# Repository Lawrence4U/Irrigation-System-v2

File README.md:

# Irrigation System using LoRa communications and Chirpstack

### KiCad

The external footprints used can be found in the [Imports](./KiCad/symbols/Imports/) folder.

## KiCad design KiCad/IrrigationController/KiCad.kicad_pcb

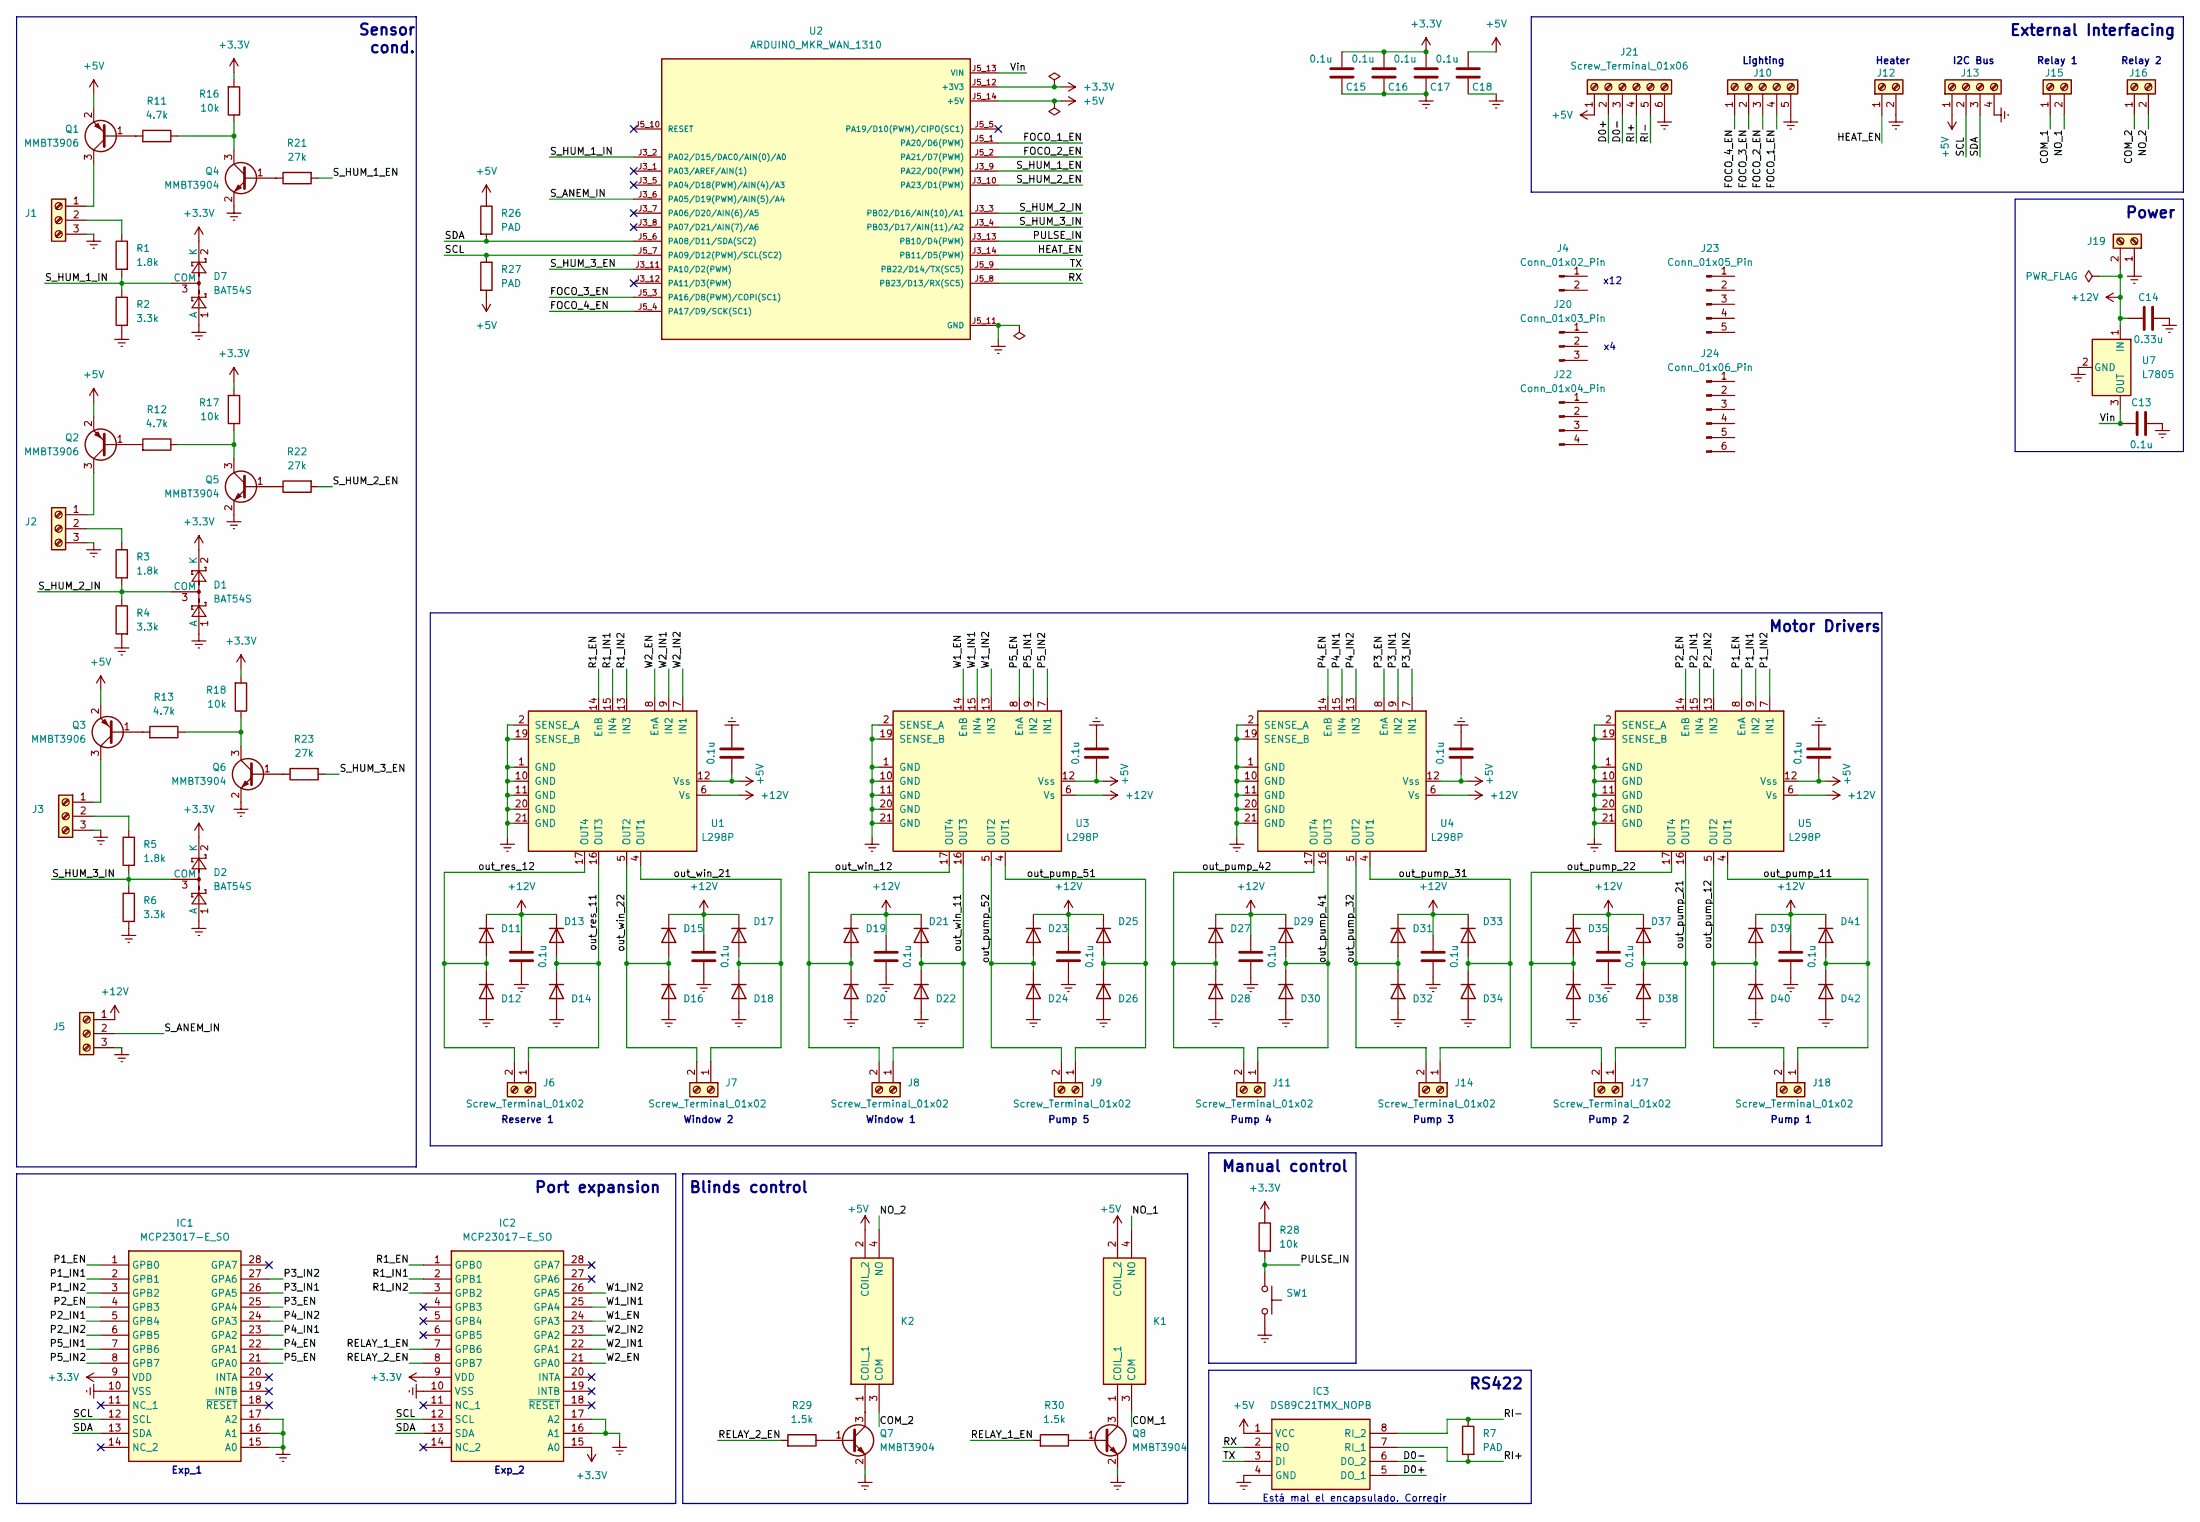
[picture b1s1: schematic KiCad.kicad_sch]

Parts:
C1, C2, C3, C4, C5, C6, C7, C8, C9, C10, C11, C12, C13, C15, C16, C17, C18: 0.1u; C_1206_3216Metric; Mouser Part Number 80-C1206X104K1RAUTO
C14: 0.33u; C_1206_3216Metric; Mouser Part Number 80-C1206X334K1RAUTO
D1, D2, D7: BAT54S; SOT-23; Mouser Part Number 637-BAT54S
D11, D12, D13, D14, D15, D16, D17, D18, D19, D20, D21, D22, D23, D24, D25, D26, D27, D28, D29, D30, D31, D32, D33, D34, D35, D36, D37, D38, D39, D40, D41, D42: SS24; D_SMB; Mouser Part Number 821-SS24
IC1, IC2: MCP23017-E_SO; SOIC127P1030X265-28N; Mouser Part Number 579-MCP23017-E/SO
IC3: DS89C21TMX_NOPB; SOIC127P600X175-8N; Mouser Part Number 926-DS89C21TMX/NOPB
J1, J2, J3, J5: Screw_Terminal_01x03; TerminalBlock_Phoenix_MKDS-1,5-3_1x03_P5.00mm_Horizontal; Mouser Part Number 710-691311700003
J4: Conn_01x02_Pin; Mouser Part Number 710-691352710002
J6, J7, J8, J9, J11, J12, J14, J15, J16, J17, J18, J19: Screw_Terminal_01x02; TerminalBlock_Phoenix_MKDS-1,5-2_1x02_P5.00mm_Horizontal; Mouser Part Number 710-691311700002
J10: Screw_Terminal_01x05; TerminalBlock_Phoenix_MKDS-1,5-5_1x05_P5.00mm_Horizontal; Mouser Part Number 710-691311700005
J13: Screw_Terminal_01x04; TerminalBlock_Phoenix_MKDS-1,5-4_1x04_P5.00mm_Horizontal; Mouser Part Number 710-691311700004
J20: Conn_01x03_Pin; Mouser Part Number 710-691352710003
J21: Screw_Terminal_01x06; TerminalBlock_Phoenix_MKDS-1,5-6_1x06_P5.00mm_Horizontal; Mouser Part Number 710-691311700006
J22: Conn_01x04_Pin; Mouser Part Number 710-691352710004
J23: Conn_01x05_Pin; Mouser Part Number 710-691352710005
J24: Conn_01x06_Pin; Mouser Part Number 710-691352710006
K1, K2: 2071556-9; 20715569; Mouser Part Number 655-2071556-9
Q1, Q2, Q3: MMBT3906; SOT-23
Q4, Q5, Q6, Q7, Q8: MMBT3904; SOT-23
R1, R3, R5: 1.8k; R_1206_3216Metric; Mouser Part Number 603-RT1206FRE071K8L
R2, R4, R6: 3.3k; R_1206_3216Metric; Mouser Part Number 603-RT1206FRE073K3L
R7, R26, R27: PAD; R_1206_3216Metric
R11, R12, R13: 4.7k; R_1206_3216Metric; Mouser Part Number 603-RT1206FRE074K7L
R16, R17, R18, R28: 10k; R_1206_3216Metric; Mouser Part Number 603-RT1206FRE1310KL
R21, R22, R23: 27k; R_1206_3216Metric; Mouser Part Number 603-RT1206FRE0727KL
R29, R30: 1.5k; R_1206_3216Metric; Mouser Part Number 603-RT1206FRE071K5L
SW1: SW_Push; SW_PUSH_6mm_H4.3mm
U1, U3, U4, U5: L298P; HSOP-20-1EP_11.0x15.9mm_P1.27mm_SlugDown_ThermalVias; Mouser Part Number 511-L298P
U2: ARDUINO_MKR_WAN_1310; BOARD_ARDUINO_MKR_WAN_1310; PARTREV 06/27/2019
U7: L7805; TO-263-2; Mouser Part Number 511-L7805ABD2T-TR

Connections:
+5V: C3.1, C6.1, C9.1, C12.1, C18.1, IC3.1 (VCC), J13.1, J21.1, K1.2 (COIL_2), K2.2 (COIL_2), Q1.2 (E), Q2.2 (E), Q3.2 (E), R26.1, R27.2, U1.12 (Vss), U2.J5_14 (+5V), U3.12 (Vss), U4.12 (Vss), U5.12 (Vss)
+12V: C1.1, C2.1, C4.1, C5.1, C7.1, C8.1, C10.1, C11.1, C14.1, D11.1 (K), D13.1 (K), D15.1 (K), D17.1 (K), D19.1 (K), D21.1 (K), D23.1 (K), D25.1 (K), D27.1 (K), D29.1 (K), D31.1 (K), D33.1 (K), D35.1 (K), D37.1 (K), D39.1 (K), D41.1 (K), J5.1, J19.2, U1.6 (Vs), U3.6 (Vs), U4.6 (Vs), U5.6 (Vs), U7.1 (IN)
/COM_1: J15.1, K1.3 (COM)
/COM_2: J16.1, K2.3 (COM)
/D0+: IC3.5 (DO_1), J21.2
/D0-: IC3.6 (DO_2), J21.3
/FOCO_1_EN: J10.4, U2.J5_1 (PA20/D6(PWM))
/FOCO_2_EN: J10.3, U2.J5_2 (PA21/D7(PWM))
/FOCO_3_EN: J10.2, U2.J5_3 (PA16/D8(PWM)/COPI(SC1))
/FOCO_4_EN: J10.1, U2.J5_4 (PA17/D9/SCK(SC1))
/HEAT_EN: J12.1, U2.J3_14 (PB11/D5(PWM))
/NO_1: J15.2, K1.4 (NO)
/NO_2: J16.2, K2.4 (NO)
/P1_EN: IC1.1 (GPB0), U5.8 (EnA)
/P1_IN1: IC1.2 (GPB1), U5.9 (IN2)
/P1_IN2: IC1.3 (GPB2), U5.7 (IN1)
/P2_EN: IC1.4 (GPB3), U5.14 (EnB)
/P2_IN1: IC1.5 (GPB4), U5.15 (IN4)
/P2_IN2: IC1.6 (GPB5), U5.13 (IN3)
/P3_EN: IC1.25 (GPA4), U4.8 (EnA)
/P3_IN1: IC1.26 (GPA5), U4.9 (IN2)
/P3_IN2: IC1.27 (GPA6), U4.7 (IN1)
/P4_EN: IC1.22 (GPA1), U4.14 (EnB)
/P4_IN1: IC1.23 (GPA2), U4.15 (IN4)
/P4_IN2: IC1.24 (GPA3), U4.13 (IN3)
/P5_EN: IC1.21 (GPA0), U3.8 (EnA)
/P5_IN1: IC1.7 (GPB6), U3.9 (IN2)
/P5_IN2: IC1.8 (GPB7), U3.7 (IN1)
/PULSE_IN: R28.2, SW1.1, U2.J3_13 (PB10/D4(PWM))
/R1_EN: IC2.1 (GPB0), U1.14 (EnB)
/R1_IN1: IC2.2 (GPB1), U1.15 (IN4)
/R1_IN2: IC2.3 (GPB2), U1.13 (IN3)
/RELAY_1_EN: IC2.7 (GPB6), R30.2
/RELAY_2_EN: IC2.8 (GPB7), R29.2
/RI+: IC3.7 (RI_1), J21.4, R7.2
/RI-: IC3.8 (RI_2), J21.5, R7.1
/RX: IC3.2 (RO), U2.J5_8 (PB23/D13/RX(SC5))
/SCL: IC1.12 (SCL), IC2.12 (SCL), J13.2, R27.1, U2.J5_7 (PA09/D12(PWM)/SCL(SC2))
/SDA: IC1.13 (SDA), IC2.13 (SDA), J13.3, R26.2, U2.J5_6 (PA08/D11/SDA(SC2))
/S_ANEM_IN: J5.2, U2.J3_6 (PA05/D19(PWM)/AIN(5)/A4)
/S_HUM_1_EN: R21.2, U2.J3_9 (PA22/D0(PWM))
/S_HUM_1_IN: D7.3 (COM), R1.2, R2.1, U2.J3_2 (PA02/D15/DAC0/AIN(0)/A0)
/S_HUM_2_EN: R22.2, U2.J3_10 (PA23/D1(PWM))
/S_HUM_2_IN: D1.3 (COM), R3.2, R4.1, U2.J3_3 (PB02/D16/AIN(10)/A1)
/S_HUM_3_EN: R23.2, U2.J3_11 (PA10/D2(PWM))
/S_HUM_3_IN: D2.3 (COM), R5.2, R6.1, U2.J3_4 (PB03/D17/AIN(11)/A2)
/TX: IC3.3 (DI), U2.J5_9 (PB22/D14/TX(SC5))
/W1_EN: IC2.24 (GPA3), U3.14 (EnB)
/W1_IN1: IC2.25 (GPA4), U3.15 (IN4)
/W1_IN2: IC2.26 (GPA5), U3.13 (IN3)
/W2_EN: IC2.21 (GPA0), U1.8 (EnA)
/W2_IN1: IC2.22 (GPA1), U1.9 (IN2)
/W2_IN2: IC2.23 (GPA2), U1.7 (IN1)
/out_pump_11: D41.2 (A), D42.1 (K), J18.1, U5.4 (OUT1)
/out_pump_12: D39.2 (A), D40.1 (K), J18.2, U5.5 (OUT2)
/out_pump_21: D37.2 (A), D38.1 (K), J17.1, U5.16 (OUT3)
/out_pump_22: D35.2 (A), D36.1 (K), J17.2, U5.17 (OUT4)
/out_pump_31: D33.2 (A), D34.1 (K), J14.1, U4.4 (OUT1)
/out_pump_32: D31.2 (A), D32.1 (K), J14.2, U4.5 (OUT2)
/out_pump_41: D29.2 (A), D30.1 (K), J11.1, U4.16 (OUT3)
/out_pump_42: D27.2 (A), D28.1 (K), J11.2, U4.17 (OUT4)
/out_pump_51: D25.2 (A), D26.1 (K), J9.1, U3.4 (OUT1)
/out_pump_52: D23.2 (A), D24.1 (K), J9.2, U3.5 (OUT2)
/out_res_11: D13.2 (A), D14.1 (K), J6.1, U1.16 (OUT3)
/out_res_12: D11.2 (A), D12.1 (K), J6.2, U1.17 (OUT4)
/out_win_11: D21.2 (A), D22.1 (K), J8.1, U3.16 (OUT3)
/out_win_12: D19.2 (A), D20.1 (K), J8.2, U3.17 (OUT4)
/out_win_21: D17.2 (A), D18.1 (K), J7.1, U1.4 (OUT1)
/out_win_22: D15.2 (A), D16.1 (K), J7.2, U1.5 (OUT2)
unnamed: J1.1, Q1.3 (C)
unnamed: J1.2, R1.1
unnamed: J2.1, Q2.3 (C)
unnamed: J2.2, R3.1
unnamed: J3.1, Q3.3 (C)
unnamed: J3.2, R5.1
unnamed: K1.1 (COIL_1), Q8.3 (C)
unnamed: K2.1 (COIL_1), Q7.3 (C)
unnamed: Q1.1 (B), R11.2
unnamed: Q2.1 (B), R12.2
unnamed: Q3.1 (B), R13.2
unnamed: Q4.1 (B), R21.1
unnamed: Q4.3 (C), R11.1, R16.1
unnamed: Q5.1 (B), R22.1
unnamed: Q5.3 (C), R12.1, R17.1
unnamed: Q6.1 (B), R23.1
unnamed: Q6.3 (C), R13.1, R18.1
unnamed: Q7.1 (B), R29.1
unnamed: Q8.1 (B), R30.1

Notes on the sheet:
Sensor cond.
Window 1
RS422
Lighting
I2C Bus
Pump 4
x12
Pump 3
Manual control
Heater
Pump 5
Reserve 1
Blinds control
Window 2
Exp_2
Relay 1
Pump 2
External Interfacing
Relay 2
Exp_1
Power
Pump 1
Motor Drivers
Port expansion
Está mal el encapsulado. Corregir

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
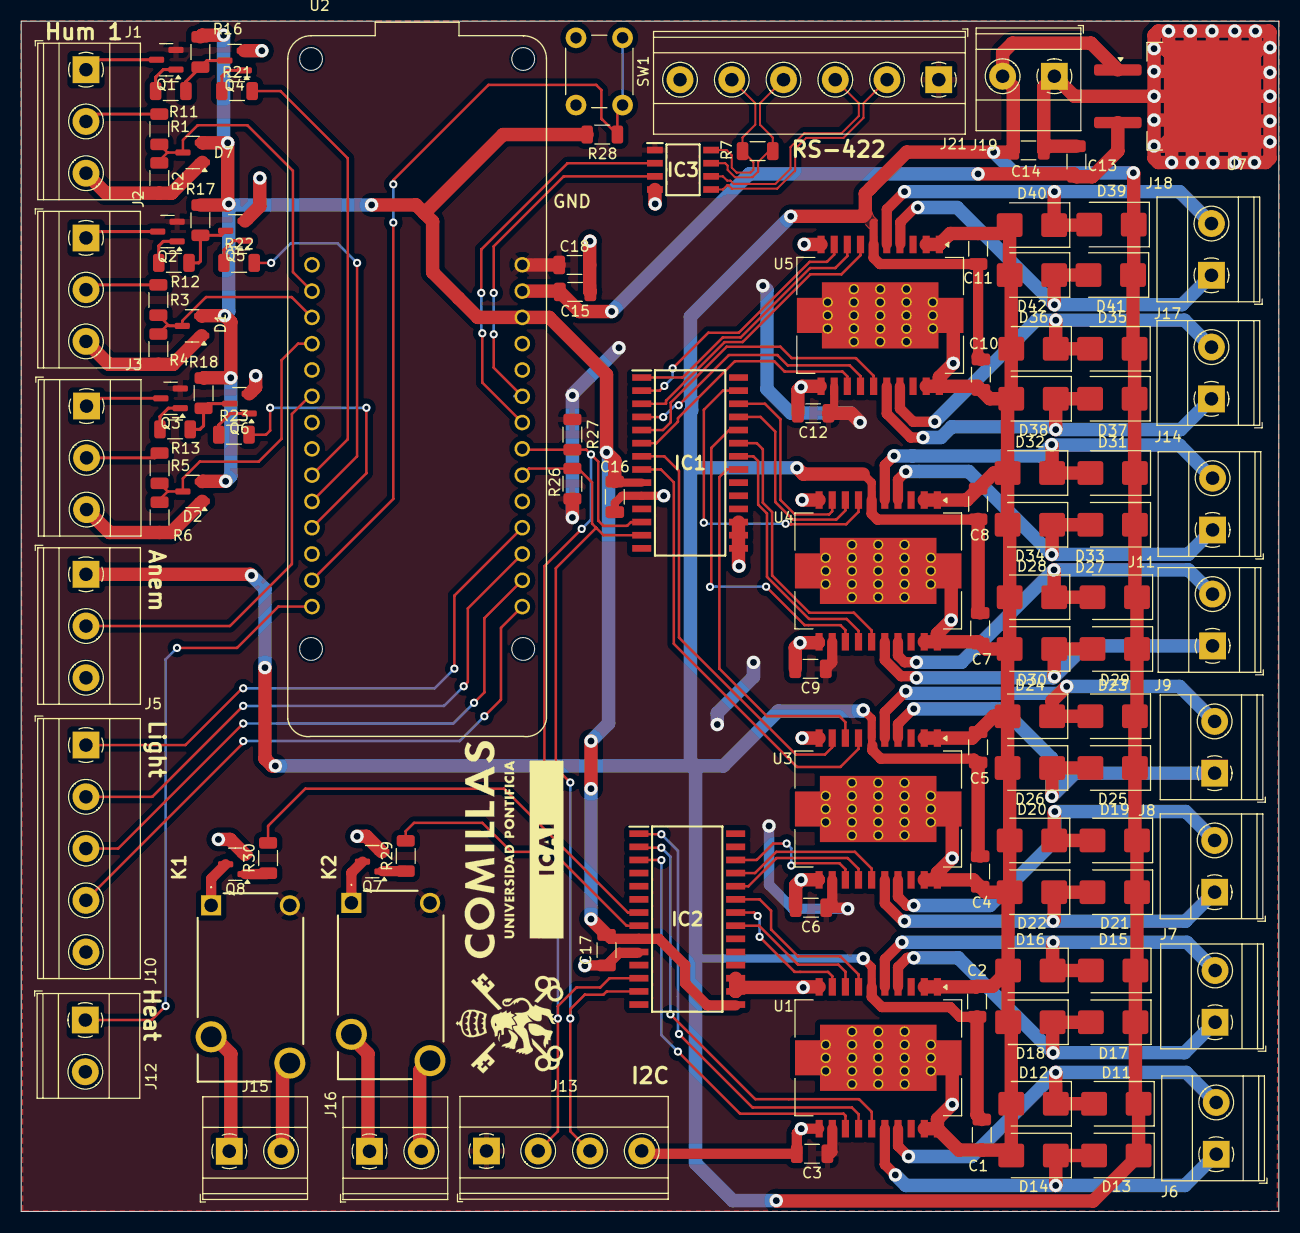
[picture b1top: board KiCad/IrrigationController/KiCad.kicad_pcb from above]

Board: 2 copper layers, 121.5 x 115.0 mm, 113 parts (0 on the bottom side), 91 nets.

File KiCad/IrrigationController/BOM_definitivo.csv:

Reference,Value,Qty,DNP,Manufacturer_Part_Number,Mouser Part Number,
"C1,C2,C3,C4,C5,C6,C7,C8,C9,C10,C11,C12,C13,C16,C17,C18",0.1u,16,,,80-C1206X104K1RAUTO,
C14,0.33u,1,,,80-C1206X334K1RAUTO,
"D1,D2,D7",BAT54S,3,,,637-BAT54S,
"D11,D12,D13,D14,D15,D16,D17,D18,D19,D20,D21,D22,D23,D24,D25,D26,D27,D28,D29,D30,D31,D32,D33,D34,D35,D36,D37,D38,D39,D40,D41,D42",SS24,32,,,821-SS24,
"IC1,IC2",MCP23017-E_SO,2,,MCP23017-E/SO,579-MCP23017-E/SO,
IC3,DS89C21TMX_NOPB,1,,DS89C21TMX/NOPB,926-DS89C21TMX/NOPB,
"J1,J2,J3,J5",Screw_Terminal_01x03,4,,,710-691311700003,
J4,Conn_01x02_Pin,12,,, 710-691352710002,"Borna para J6, J7, etc"
"J6,J7,J8,J9,J11,J12,J14,J15,J16,J17,J18,J19",Screw_Terminal_01x02,12,,,710-691311700002,
J10,Screw_Terminal_01x05,1,,, 710-691311700005,
J13,Screw_Terminal_01x04,1,,, 710-691311700004,
J20,Conn_01x03_Pin,4,,, 710-691352710003,"Borna para J1, J2, etc."
J21,Screw_Terminal_01x06,1,,,710-691311700006,
J22,Conn_01x04_Pin,1,,, 710-691352710004,Borna para J13
J23,Conn_01x05_Pin,1,,, 710-691352710005,Borna para J10
J24,Conn_01x06_Pin,1,,, 710-691352710006,Borna para J21
"K1,K2",2071556-9,2,,2071556-9,655-2071556-9,
"Q1,Q2,Q3",MMBT3906,3,,,637-MMBT3906,
"Q6,Q7,Q8,Q11,Q12",MMBT3904,5,,,637-MMBT3904-AQ,
"R1,R3,R5",1.8k,3,,,603-RT1206FRE071K8L,
"R2,R4,R6",3.3k,3,,,603-RT1206FRE073K3L,
"R7,R26,R27",PAD,3,,,CRCW1206120RFKEAC ,"Resistencia de 120 Ohm, por si acaso."
"R11,R12,R13",4.7k,3,,,603-RT1206FRE074K7L,
"R16,R17,R18,R28",10k,4,,,603-RT1206FRE1310KL,
"R21,R22,R23",27k,3,,,603-RT1206FRE0727KL,
"R29,R30",1.5k,2,,,603-RT1206FRE071K5L,
SW1,SW_Push,1,,,,
"U1,U3,U4,U5",L298P,4,,,511-L298P,
U2,ARDUINO_MKR_WAN_1310,1,,,,
U7,L7805,1,,,511-L7805ABD2T-TR,

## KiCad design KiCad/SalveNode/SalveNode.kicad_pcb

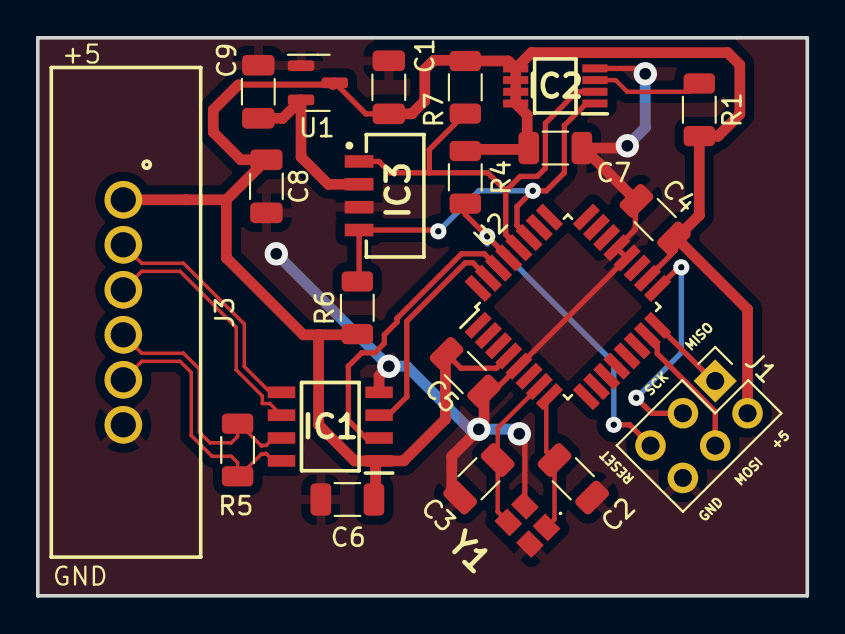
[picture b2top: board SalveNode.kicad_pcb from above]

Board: 2 copper layers, 42.8 x 31.0 mm, 22 parts (0 on the bottom side), 17 nets.

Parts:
C1, C9: 1u; C_1206_3216Metric
C2, C3: 12p; C_1206_3216Metric
C4, C5, C6, C7, C8: 100n; C_1206_3216Metric
IC1: DS89C21TMX_NOPB; SOIC127P600X175-8N
IC2: TMP75AQDGKRQ1; SOP65P490X110-8N
IC3: VEML7700-TR; VEML7700
J1: AVR-ISP-6; PinHeader_2x03_P2.54mm_Vertical
J3: 691382030006
R1: 5k; R_1206_3216Metric
R4: 10k; R_1206_3216Metric
R5: PAD; R_1206_3216Metric
R6, R7: 4.7k; R_1206_3216Metric
U1: MCP1700x-330xxTT; SOT-23
U2: ATmega328PB-A; TQFP-32_7x7mm_P0.8mm
Y1: 16M; ECS1601036CKMTR3

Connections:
+3.3V: C9.2, IC3.2 (VDD), U1.2 (VO)
+5V: C1.2, C4.2, C5.2, C6.2, C7.2, C8.2, IC1.1 (VCC), IC2.5 (A2), IC2.6 (A1), IC2.7 (A0), IC2.8 (V+), J1.2 (VCC), J3.1, R1.2, R4.2, R6.1, R7.2, U1.3 (VI), U2.4 (VCC), U2.18 (AVCC)
/D0+: IC1.6 (DO_2), J3.3
/D0-: IC1.5 (DO_1), J3.2
/MISO: J1.1 (MISO), U2.16 (PB4)
/MOSI: J1.4 (MOSI), U2.15 (PB3)
/RESET: J1.5 (~RST), R4.1, U2.29 (~RESET/PC6)
/RI+: IC1.8 (RI_2), J3.5, R5.1
/RI-: IC1.7 (RI_1), J3.4, R5.2
/RX: IC1.2 (RO), U2.30 (PD0)
/SCK: J1.3 (SCK), U2.17 (PB5)
/SCL: IC2.2 (SCL), IC3.1 (SCL), R7.1, U2.28 (PC5)
/SDA: IC2.1 (SDA), IC3.4 (SDA), R6.2, U2.27 (PC4)
/TX: IC1.3 (DI), U2.31 (PD1)
/XTAL1: C3.2, U2.7 (XTAL1/PB6), Y1.3
/XTAL2: C2.2, U2.8 (XTAL2/PB7), Y1.1
Earth: C1.1, C2.1, C3.1, C4.1, C5.1, C6.1, C7.1, C8.1, C9.1, IC1.4 (GND), IC2.4 (GND), IC3.3 (GND), J1.6 (GND), J3.6, U1.1 (GND), U2.5 (GND), U2.20 (AREF), U2.21 (GND), Y1.2, Y1.4

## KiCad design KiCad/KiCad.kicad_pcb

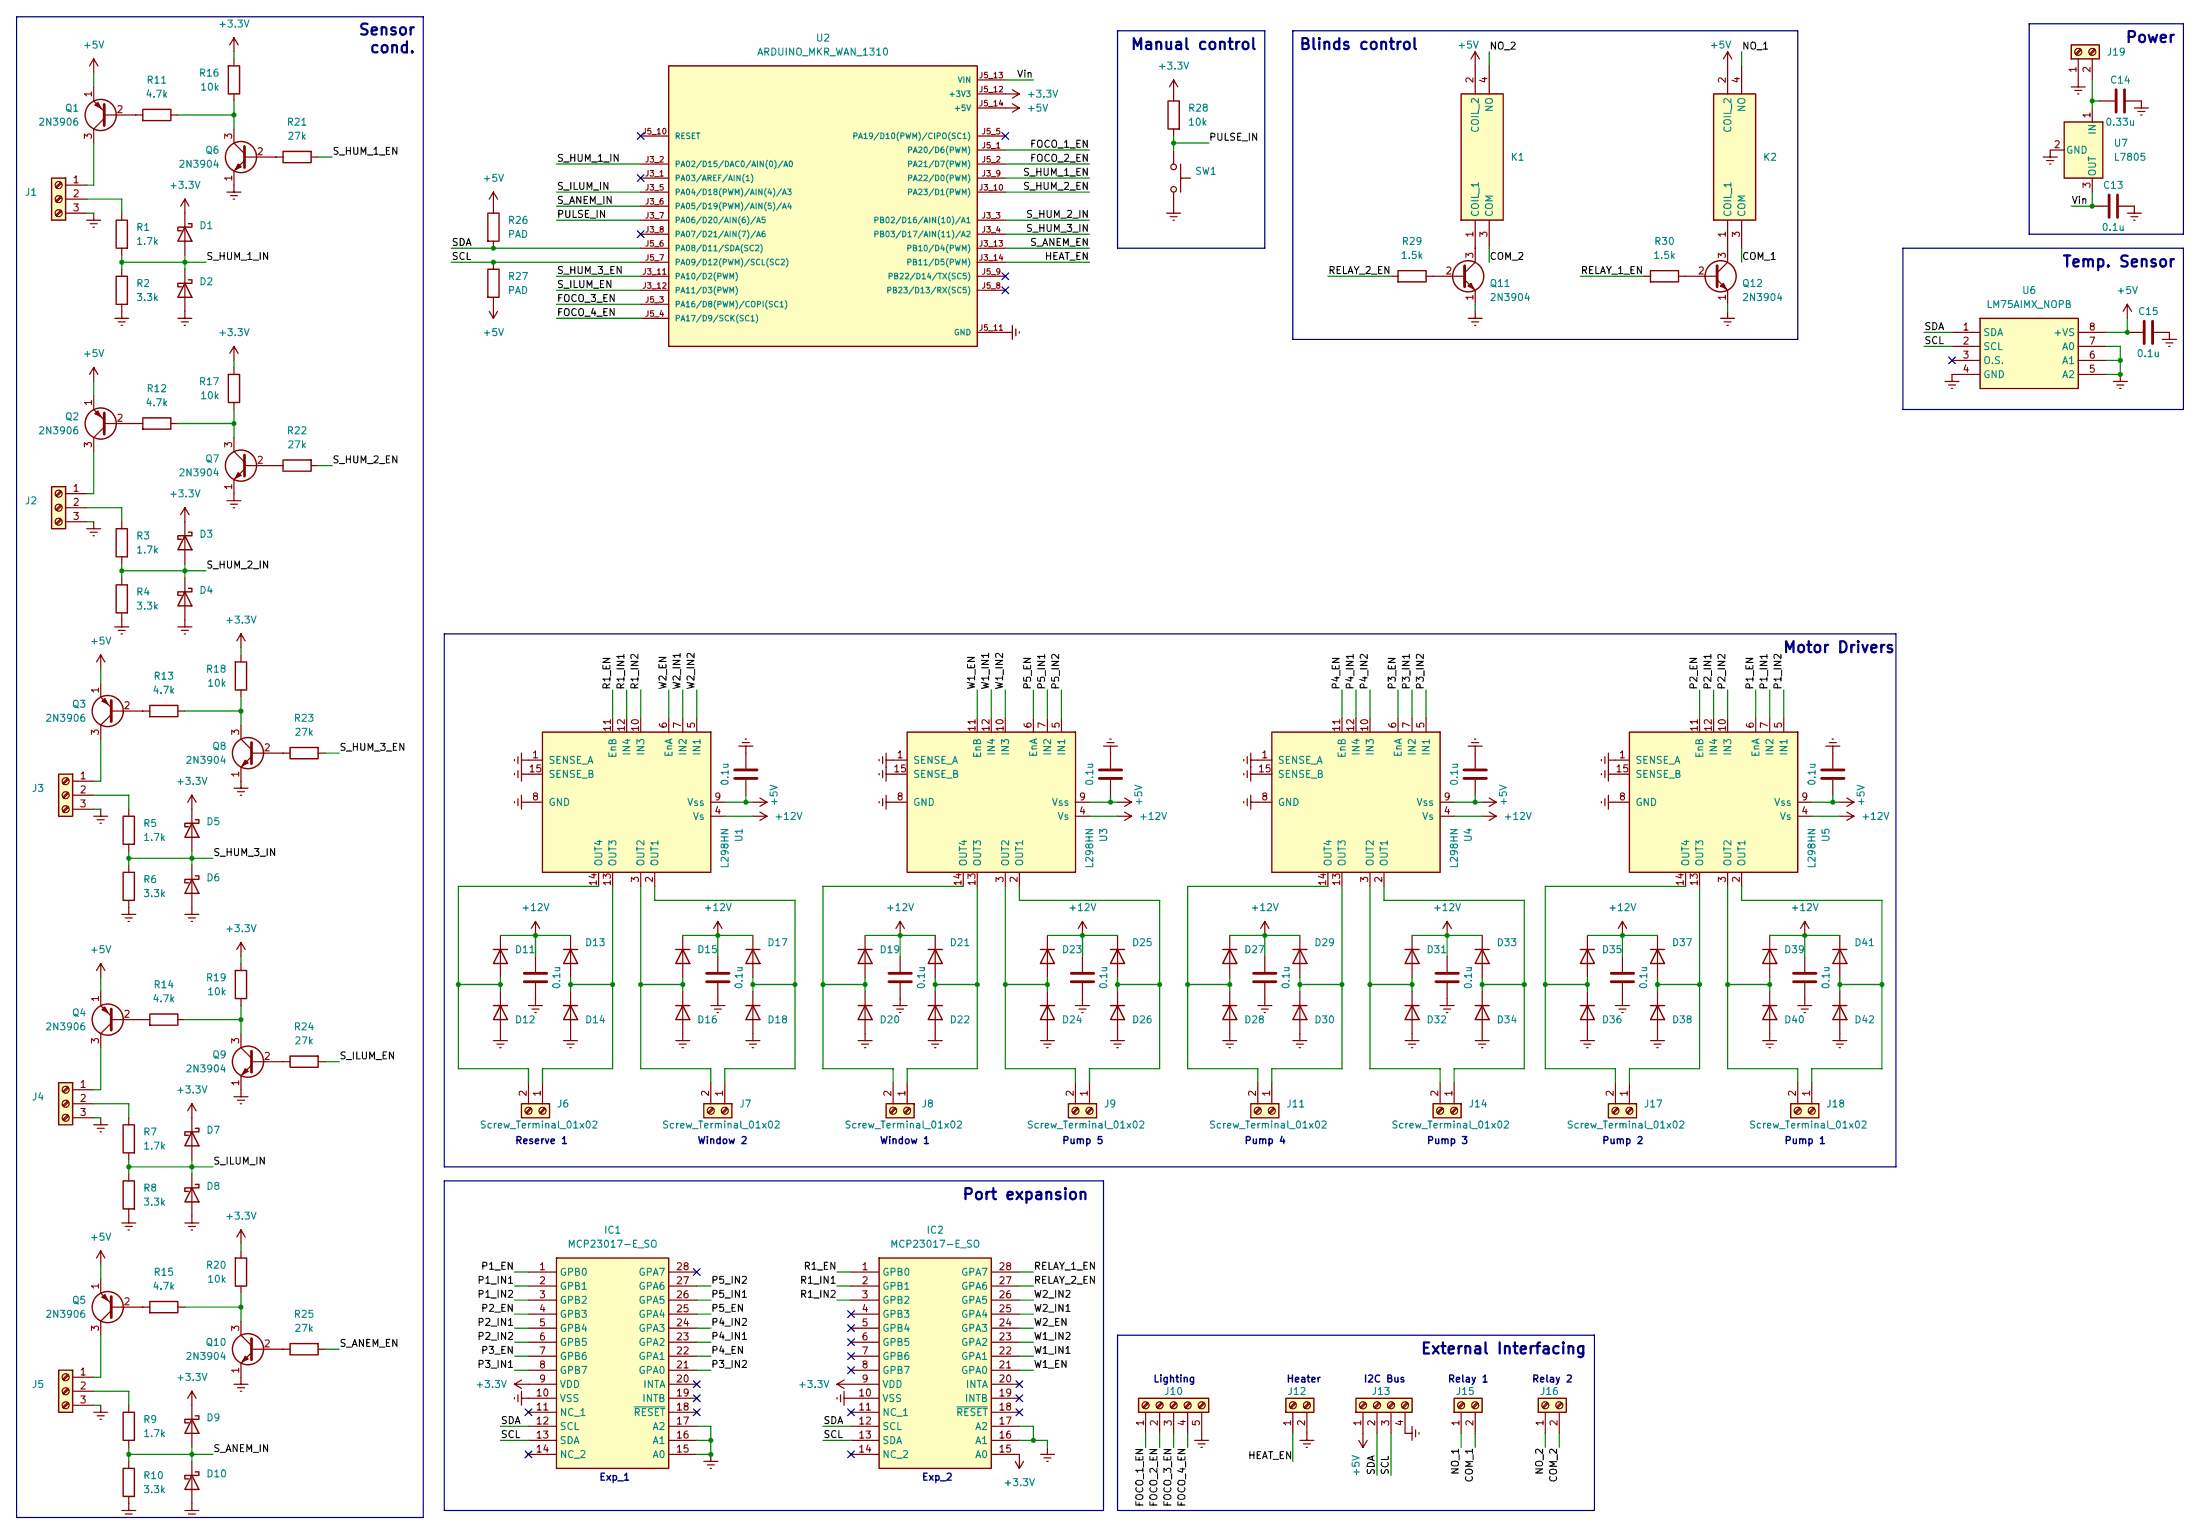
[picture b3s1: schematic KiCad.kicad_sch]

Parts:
C1, C2, C3, C4, C5, C6, C7, C8, C9, C10, C11, C12, C13, C15: 0.1u; C_1206_3216Metric_Pad1.33x1.80mm_HandSolder
C14: 0.33u; C_1206_3216Metric_Pad1.33x1.80mm_HandSolder
D1, D2, D3, D4, D5, D6, D7, D8, D9, D10: 1N5711UR; D_1206_3216Metric_Pad1.42x1.75mm_HandSolder
D11, D12, D13, D14, D15, D16, D17, D18, D19, D20, D21, D22, D23, D24, D25, D26, D27, D28, D29, D30, D31, D32, D33, D34, D35, D36, D37, D38, D39, D40, D41, D42: 1N4007; D_1206_3216Metric_Pad1.42x1.75mm_HandSolder
IC1, IC2: MCP23017-E_SO; SOIC127P1030X265-28N; Mouser Part Number 579-MCP23017-E/SO
J1, J2, J3, J4, J5: Screw_Terminal_01x03; TerminalBlock_Phoenix_MKDS-1,5-3_1x03_P5.00mm_Horizontal
J6, J7, J8, J9, J11, J12, J14, J15, J16, J17, J18, J19: Screw_Terminal_01x02; TerminalBlock_Phoenix_MKDS-1,5-2_1x02_P5.00mm_Horizontal
J10: Screw_Terminal_01x05; TerminalBlock_Phoenix_MKDS-1,5-5_1x05_P5.00mm_Horizontal
J13: Screw_Terminal_01x04; TerminalBlock_Phoenix_MKDS-1,5-4_1x04_P5.00mm_Horizontal
K1, K2: 2071556-9; 20715569; Mouser Part Number 655-2071556-9
Q1, Q2, Q3, Q4, Q5: 2N3906; SOT-23
Q6, Q7, Q8, Q9, Q10, Q11, Q12: 2N3904; SOT-23
R1, R3, R5, R7, R9: 1.7k; R_1206_3216Metric_Pad1.30x1.75mm_HandSolder
R2, R4, R6, R8, R10: 3.3k; R_1206_3216Metric_Pad1.30x1.75mm_HandSolder
R11, R12, R13, R14, R15: 4.7k; R_1206_3216Metric_Pad1.30x1.75mm_HandSolder
R16, R17, R18, R19, R20, R28: 10k; R_1206_3216Metric_Pad1.30x1.75mm_HandSolder
R21, R22, R23, R24, R25: 27k; R_1206_3216Metric_Pad1.30x1.75mm_HandSolder
R26, R27: PAD; R_1206_3216Metric_Pad1.30x1.75mm_HandSolder
R29, R30: 1.5k; R_1206_3216Metric_Pad1.30x1.75mm_HandSolder
SW1: SW_Push; SW_PUSH_6mm_H4.3mm
U1, U3, U4, U5: L298HN; TO-220-15_P2.54x2.54mm_StaggerOdd_Lead4.58mm_Vertical
U2: ARDUINO_MKR_WAN_1310; BOARD_ARDUINO_MKR_WAN_1310; PARTREV 06/27/2019
U6: LM75AIMX_NOPB; SOIC127P600X175-8N; Mouser Part Number 926-LM75AIMX/NOPB
U7: L7805; TO-220-3_Vertical

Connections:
+5V: C3.1, C6.1, C9.1, C12.1, C15.1, J13.1, K1.2 (COIL_2), K2.2 (COIL_2), Q1.1 (E), Q2.1 (E), Q3.1 (E), Q4.1 (E), Q5.1 (E), R26.1, R27.2, U1.9 (Vss), U2.J5_14 (+5V), U3.9 (Vss), U4.9 (Vss), U5.9 (Vss), U6.8 (+VS)
+12V: C1.1, C2.1, C4.1, C5.1, C7.1, C8.1, C10.1, C11.1, D11.1 (K), D13.1 (K), D15.1 (K), D17.1 (K), D19.1 (K), D21.1 (K), D23.1 (K), D25.1 (K), D27.1 (K), D29.1 (K), D31.1 (K), D33.1 (K), D35.1 (K), D37.1 (K), D39.1 (K), D41.1 (K), U1.4 (Vs), U3.4 (Vs), U4.4 (Vs), U5.4 (Vs)
/COM_1: J15.2, K2.3 (COM)
/COM_2: J16.2, K1.3 (COM)
/FOCO_1_EN: J10.1, U2.J5_1 (PA20/D6(PWM))
/FOCO_2_EN: J10.2, U2.J5_2 (PA21/D7(PWM))
/FOCO_3_EN: J10.3, U2.J5_3 (PA16/D8(PWM)/COPI(SC1))
/FOCO_4_EN: J10.4, U2.J5_4 (PA17/D9/SCK(SC1))
/HEAT_EN: J12.1, U2.J3_14 (PB11/D5(PWM))
/NO_1: J15.1, K2.4 (NO)
/NO_2: J16.1, K1.4 (NO)
/P1_EN: IC1.1 (GPB0), U5.6 (EnA)
/P1_IN1: IC1.2 (GPB1), U5.7 (IN2)
/P1_IN2: IC1.3 (GPB2), U5.5 (IN1)
/P2_EN: IC1.4 (GPB3), U5.11 (EnB)
/P2_IN1: IC1.5 (GPB4), U5.12 (IN4)
/P2_IN2: IC1.6 (GPB5), U5.10 (IN3)
/P3_EN: IC1.7 (GPB6), U4.6 (EnA)
/P3_IN1: IC1.8 (GPB7), U4.7 (IN2)
/P3_IN2: IC1.21 (GPA0), U4.5 (IN1)
/P4_EN: IC1.22 (GPA1), U4.11 (EnB)
/P4_IN1: IC1.23 (GPA2), U4.12 (IN4)
/P4_IN2: IC1.24 (GPA3), U4.10 (IN3)
/P5_EN: IC1.25 (GPA4), U3.6 (EnA)
/P5_IN1: IC1.26 (GPA5), U3.7 (IN2)
/P5_IN2: IC1.27 (GPA6), U3.5 (IN1)
/PULSE_IN: R28.2, SW1.1, U2.J3_7 (PA06/D20/AIN(6)/A5)
/R1_EN: IC2.1 (GPB0), U1.11 (EnB)
/R1_IN1: IC2.2 (GPB1), U1.12 (IN4)
/R1_IN2: IC2.3 (GPB2), U1.10 (IN3)
/RELAY_1_EN: IC2.28 (GPA7), R30.2
/RELAY_2_EN: IC2.27 (GPA6), R29.2
/SCL: IC1.13 (SDA), IC2.13 (SDA), J13.3, R27.1, U2.J5_7 (PA09/D12(PWM)/SCL(SC2)), U6.2 (SCL)
/SDA: IC1.12 (SCL), IC2.12 (SCL), J13.2, R26.2, U2.J5_6 (PA08/D11/SDA(SC2)), U6.1 (SDA)
/S_ANEM_EN: R25.2, U2.J3_13 (PB10/D4(PWM))
/S_ANEM_IN: D9.2 (A), D10.1 (K), R9.2, R10.1, U2.J3_6 (PA05/D19(PWM)/AIN(5)/A4)
/S_HUM_1_EN: R21.2, U2.J3_9 (PA22/D0(PWM))
/S_HUM_1_IN: D1.2 (A), D2.1 (K), R1.2, R2.1, U2.J3_2 (PA02/D15/DAC0/AIN(0)/A0)
/S_HUM_2_EN: R22.2, U2.J3_10 (PA23/D1(PWM))
/S_HUM_2_IN: D3.2 (A), D4.1 (K), R3.2, R4.1, U2.J3_3 (PB02/D16/AIN(10)/A1)
/S_HUM_3_EN: R23.2, U2.J3_11 (PA10/D2(PWM))
/S_HUM_3_IN: D5.2 (A), D6.1 (K), R5.2, R6.1, U2.J3_4 (PB03/D17/AIN(11)/A2)
/S_ILUM_EN: R24.2, U2.J3_12 (PA11/D3(PWM))
/S_ILUM_IN: D7.2 (A), D8.1 (K), R7.2, R8.1, U2.J3_5 (PA04/D18(PWM)/AIN(4)/A3)
/Vin: C13.1, U2.J5_13 (VIN), U7.3 (OUT)
/W1_EN: IC2.21 (GPA0), U3.11 (EnB)
/W1_IN1: IC2.22 (GPA1), U3.12 (IN4)
/W1_IN2: IC2.23 (GPA2), U3.10 (IN3)
/W2_EN: IC2.24 (GPA3), U1.6 (EnA)
/W2_IN1: IC2.25 (GPA4), U1.7 (IN2)
/W2_IN2: IC2.26 (GPA5), U1.5 (IN1)
Earth: C1.2, C2.2, C3.2, C4.2, C5.2, C6.2, C7.2, C8.2, C9.2, C10.2, C11.2, C12.2, C13.2, C14.2, C15.2, D2.2 (A), D4.2 (A), D6.2 (A), D8.2 (A), D10.2 (A), D12.2 (A), D14.2 (A), D16.2 (A), D18.2 (A), D20.2 (A), D22.2 (A), D24.2 (A), D26.2 (A), D28.2 (A), D30.2 (A), D32.2 (A), D34.2 (A), D36.2 (A), D38.2 (A), D40.2 (A), D42.2 (A), IC1.10 (VSS), IC1.15 (A0), IC1.16 (A1), IC1.17 (A2), IC2.10 (VSS), IC2.16 (A1), IC2.17 (A2), J1.3, J2.3, J3.3, J4.3, J5.3, J10.5, J12.2, J13.4, J19.1, Q6.1 (E), Q7.1 (E), Q8.1 (E), Q9.1 (E), Q10.1 (E), Q11.1 (E), Q12.1 (E), R2.2, R4.2, R6.2, R8.2, R10.2, SW1.2, U1.1 (SENSE_A), U1.8 (GND), U1.15 (SENSE_B), U2.J5_11 (GND), U3.1 (SENSE_A), U3.8 (GND), U3.15 (SENSE_B), U4.1 (SENSE_A), U4.8 (GND), U4.15 (SENSE_B), U5.1 (SENSE_A), U5.8 (GND), U5.15 (SENSE_B), U6.4 (GND), U6.5 (A2), U6.6 (A1), U6.7 (A0), U7.2 (GND)
unnamed: D11.2 (A), D12.1 (K), J6.2, U1.14 (OUT4)
unnamed: D13.2 (A), D14.1 (K), J6.1, U1.13 (OUT3)
unnamed: D15.2 (A), D16.1 (K), J7.2, U1.3 (OUT2)
unnamed: D17.2 (A), D18.1 (K), J7.1, U1.2 (OUT1)
unnamed: D19.2 (A), D20.1 (K), J8.2, U3.14 (OUT4)
unnamed: D21.2 (A), D22.1 (K), J8.1, U3.13 (OUT3)
unnamed: D23.2 (A), D24.1 (K), J9.2, U3.3 (OUT2)
unnamed: D25.2 (A), D26.1 (K), J9.1, U3.2 (OUT1)
unnamed: D27.2 (A), D28.1 (K), J11.2, U4.14 (OUT4)
unnamed: D29.2 (A), D30.1 (K), J11.1, U4.13 (OUT3)
unnamed: D31.2 (A), D32.1 (K), J14.2, U4.3 (OUT2)
unnamed: D33.2 (A), D34.1 (K), J14.1, U4.2 (OUT1)
unnamed: D35.2 (A), D36.1 (K), J17.2, U5.14 (OUT4)
unnamed: D37.2 (A), D38.1 (K), J17.1, U5.13 (OUT3)
unnamed: D39.2 (A), D40.1 (K), J18.2, U5.3 (OUT2)
unnamed: D41.2 (A), D42.1 (K), J18.1, U5.2 (OUT1)
unnamed: J1.1, Q1.3 (C)
unnamed: J1.2, R1.1
unnamed: J2.1, Q2.3 (C)
unnamed: J2.2, R3.1
unnamed: J3.1, Q3.3 (C)
unnamed: J3.2, R5.1
unnamed: J4.1, Q4.3 (C)
unnamed: J4.2, R7.1
unnamed: J5.1, Q5.3 (C)
unnamed: J5.2, R9.1
unnamed: C14.1, J19.2, U7.1 (IN)
unnamed: K1.1 (COIL_1), Q11.3 (C)
unnamed: K2.1 (COIL_1), Q12.3 (C)
unnamed: Q1.2 (B), R11.2
unnamed: Q2.2 (B), R12.2
unnamed: Q3.2 (B), R13.2
unnamed: Q4.2 (B), R14.2
unnamed: Q5.2 (B), R15.2
unnamed: Q6.2 (B), R21.1
unnamed: Q6.3 (C), R11.1, R16.1
unnamed: Q7.2 (B), R22.1
unnamed: Q7.3 (C), R12.1, R17.1
unnamed: Q8.2 (B), R23.1
unnamed: Q8.3 (C), R13.1, R18.1
unnamed: Q9.2 (B), R24.1
unnamed: Q9.3 (C), R14.1, R19.1
unnamed: Q10.2 (B), R25.1
unnamed: Q10.3 (C), R15.1, R20.1
unnamed: Q11.2 (B), R29.1
unnamed: Q12.2 (B), R30.1

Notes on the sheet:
Sensor cond.
Window 1
Lighting
I2C Bus
Pump 4
Pump 3
Manual control
Heater
Pump 5
Temp. Sensor
Reserve 1
Blinds control
Window 2
Exp_2
Relay 1
Pump 2
External Interfacing
Relay 2
Exp_1
Power
Pump 1
Motor Drivers
Port expansion

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
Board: 2 copper layers, 130 parts (0 on the bottom side), 100 nets, no tracks yet.

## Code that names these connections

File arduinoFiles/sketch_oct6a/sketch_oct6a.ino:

#include <MKRWAN_v2.h>
#include <I2C_16Bit.h>
#include <Wire.h>
#include "arduino_secrets.h"

// analog pins definition
#define S_HUM_1_IN 0
#define S_HUM_2_IN 1
#define S_HUM_3_IN 2
#define S_ILUM_IN  3
#define S_ANEM_IN  4

//digital pins
#define S_HUM_1_EN 0
#define S_HUM_2_EN 1
#define S_HUM_3_EN 2
#define S_ILUM_EN 3
#define S_ANEM_EN 4
#define HEAT_EN 5
#define FOCO1_EN 6
#define FOCO2_EN 7
#define FOCO3_EN 8
#define FOCO4_EN 9
#define SDA 11
#define SCL 12

//expander addresses IOCON.BANK = 0
#define ADDR_EXP_1 0b0100000
#define ADDR_EXP_2 0b0100001
#define GPIOA 0x12 //value of pins 7-0
#define GPIOB 0x13
#define IODIR_A 0x00 // direction of pins 7-0. Def 1
#define IODIR_B 0x01 // [0,1] -> [output,input]


//temp sensor addresses
#define ADDR_TEMP 0b1001000
#define TEMP_READ 0b0

//pin addresses EXP_1
// B
#define P1_EN   0
#define P1_IN1  1
#define P1_IN2  2
#define P2_EN   3
#define P2_IN1  4
#define P2_IN2  5
#define P3_EN   6
#define P3_IN1  7
//A
#define P3_IN2  0
#define P4_EN   1
#define P4_IN1  2
#define P4_IN2  3
#define P5_EN   4
#define P5_IN1  5
#define P5_IN2  6

//pin addresses EXP_2
//A
#define W1_EN   0
#define W1_IN1  1
#define W1_IN2  2
#define W2_EN   3
#define W2_IN1  4
#define W2_IN2  5
//B
#define R1_EN   0
#define R1_IN1  1
#define R1_IN2  2

LoRaModem modem;
RTCZero rtc;

String appEui = SECRET_APP_EUI;
String appKey = SECRET_APP_KEY;

void setup() {
  // put your setup code here, to run once:
  Serial.begin(115200);
  while (!Serial);
  // change this to your regional band (eg. US915, AS923, ...)
  if (!modem.begin(EU868)) {
    Serial.println("Failed to start module");
    while (1) {}
  };
  Serial.print("Your module version is: ");
  Serial.println(modem.version());
  Serial.print("Your device EUI is: ");
  Serial.println(modem.deviceEUI());

  int connected = modem.joinOTAA(appEui, appKey);
  if (!connected) {
    Serial.println("Something went wrong; are you indoor? Move near a window and retry");
    while (1) {}
  }

  modem.minPollInterval(60);

}

void loop() {

}

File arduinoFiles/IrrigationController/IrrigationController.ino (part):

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#include "arduino_secrets.h"

// analog pins definition A#
#define S_HUM_1_IN A0
#define S_HUM_2_IN A1
#define S_HUM_3_IN A2
#define S_ANEM_IN  A4

//digital pins D#
#define S_HUM_1_EN 0
#define S_HUM_2_EN 1
#define S_HUM_3_EN 2
#define PULSE_IN 4
#define HEAT_EN 5
#define FOCO1_EN 6
#define FOCO2_EN 7
#define FOCO3_EN 8
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
//pin addresses of I/O expander EXP_1
//GPIOB
#define P1_EN   0 + 8 //in Adafruit_MCP23X17 libray GPIOA has 0-7 pins and B 8-15
#define P1_IN1  1 + 8
#define P1_IN2  2 + 8
#define P2_EN   3 + 8
#define P2_IN1  4 + 8
#define P2_IN2  5 + 8
#define P5_IN1  6 + 8
#define P5_IN2  7 + 8
//GPIOA
#define P5_EN  0
#define P4_EN  1
#define P4_IN1 2
#define P4_IN2 3
#define P3_EN  4
#define P3_IN1 5
#define P3_IN2 6

//pin addresses EXP_2
//GPIOA
#define W2_EN   0
#define W2_IN1  1
#define W2_IN2  2
#define W1_EN   3
#define W1_IN1  4
#define W1_IN2  5
//GPIOB
#define R1_EN      0 + 8
#define R1_IN1     1 + 8
#define R1_IN2     2 + 8
#define RELAY_1_EN 6 + 8
#define RELAY_2_EN 7 + 8

// arrays size constants for easier scaling in case of changes
#define NUM_HUM_SENSOR 3
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
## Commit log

2023-09-17 Added kicad files
2023-09-30 imp kicad
2023-10-04 more kicad
2023-10-06 addded Arduino files with definitions
2023-10-08 defines
2023-10-09 sch done
2023-10-21 config updated
2023-10-28 kicad sch finalised
2023-10-30 added missing footprints
2023-10-30 Readme updated
2023-11-02 added gitignore
2023-11-08 seleccion de anemometros y sensores de luz
2023-11-20 sch cahnges
2023-11-21 added other sch
2023-11-21 fixed err
2023-11-24 tarjeta externa añadido
2023-11-24 sch complete
2023-12-04 pcb changes
2023-12-16 PCB Complete
2023-12-28 fixed missing R for reset while programming
2023-12-30 qwer
2024-01-05 Created Arduino Files for Node + fixed missing pullup resistor for ALERT pin in tmp75
2024-01-22 BOMS
2024-02-01 BOM and PCB updated
2024-02-02 fixes 2
2024-02-10 Production
2024-02-29 pcb fix
2024-04-19 PCB created
2024-04-20 L298 as Power
2024-04-27 tracing in controller
2024-04-29 pcb rev1
2024-05-26 pcb donde
2024-05-27 Arregladas las conexiones al plano de masa
2024-06-06 rename
2024-06-16 started Arduino dev
2024-06-16 connected sensor structs + processing
2024-06-18 Añadidos los terminales a tornillo y generado el BOM
2024-06-18 modified schematics and continued development of Arduino programs
2024-06-19 fixed last minute error on PCB + continued Arduino development
2024-06-22 SerialProtocol completed + slaveNode completed | Untested
2024-06-22 Started Desktop CLient dev
2024-06-25 Añadido comentario: está mal el encapsulado de IC3
2024-06-26 Añadido C15 al esquema, que se había esfumado
2024-06-26 keeping going
2024-06-28 fixed error on I2C lines
2024-07-01 Fixed remaining mistakes | wrong transistor + rs422 footprints
2024-07-02 Firmware progress
